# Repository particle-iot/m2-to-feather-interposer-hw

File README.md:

## M.2 to Feather socket Interposer adapter

### Summary:
Many of our customers have scaled on particle using the feather form factor in order to swap out between Cellular and WiFi products. Unfortunately we are seeing challenges with Cat M1 and the modem sizes that we can offer in the feather form factor. The SA team would like to propose an interposer board between a Particle M.2 Som to an interposer board that can be inserted into a feather socket on a customers PCB.

We recognize our customers may not be able to take advantage of the interposer board if their mechanical assembly does not accommodate the addition Z height and Width required by the addition of an interposer board and an M.2 Som

The interposer board will need to replicate some of the features not found on the M.2 Soms

#### Features:
* Nano SIM Tray
* PMIC, Same PMIC on Boron
* 3.3V@1A Buck regulator like Boron
* Top or Side pressed MODE and RESET buttons
* Enable pin support
* MCO/Board outline is slightly larger than a feather board due to SMT header.

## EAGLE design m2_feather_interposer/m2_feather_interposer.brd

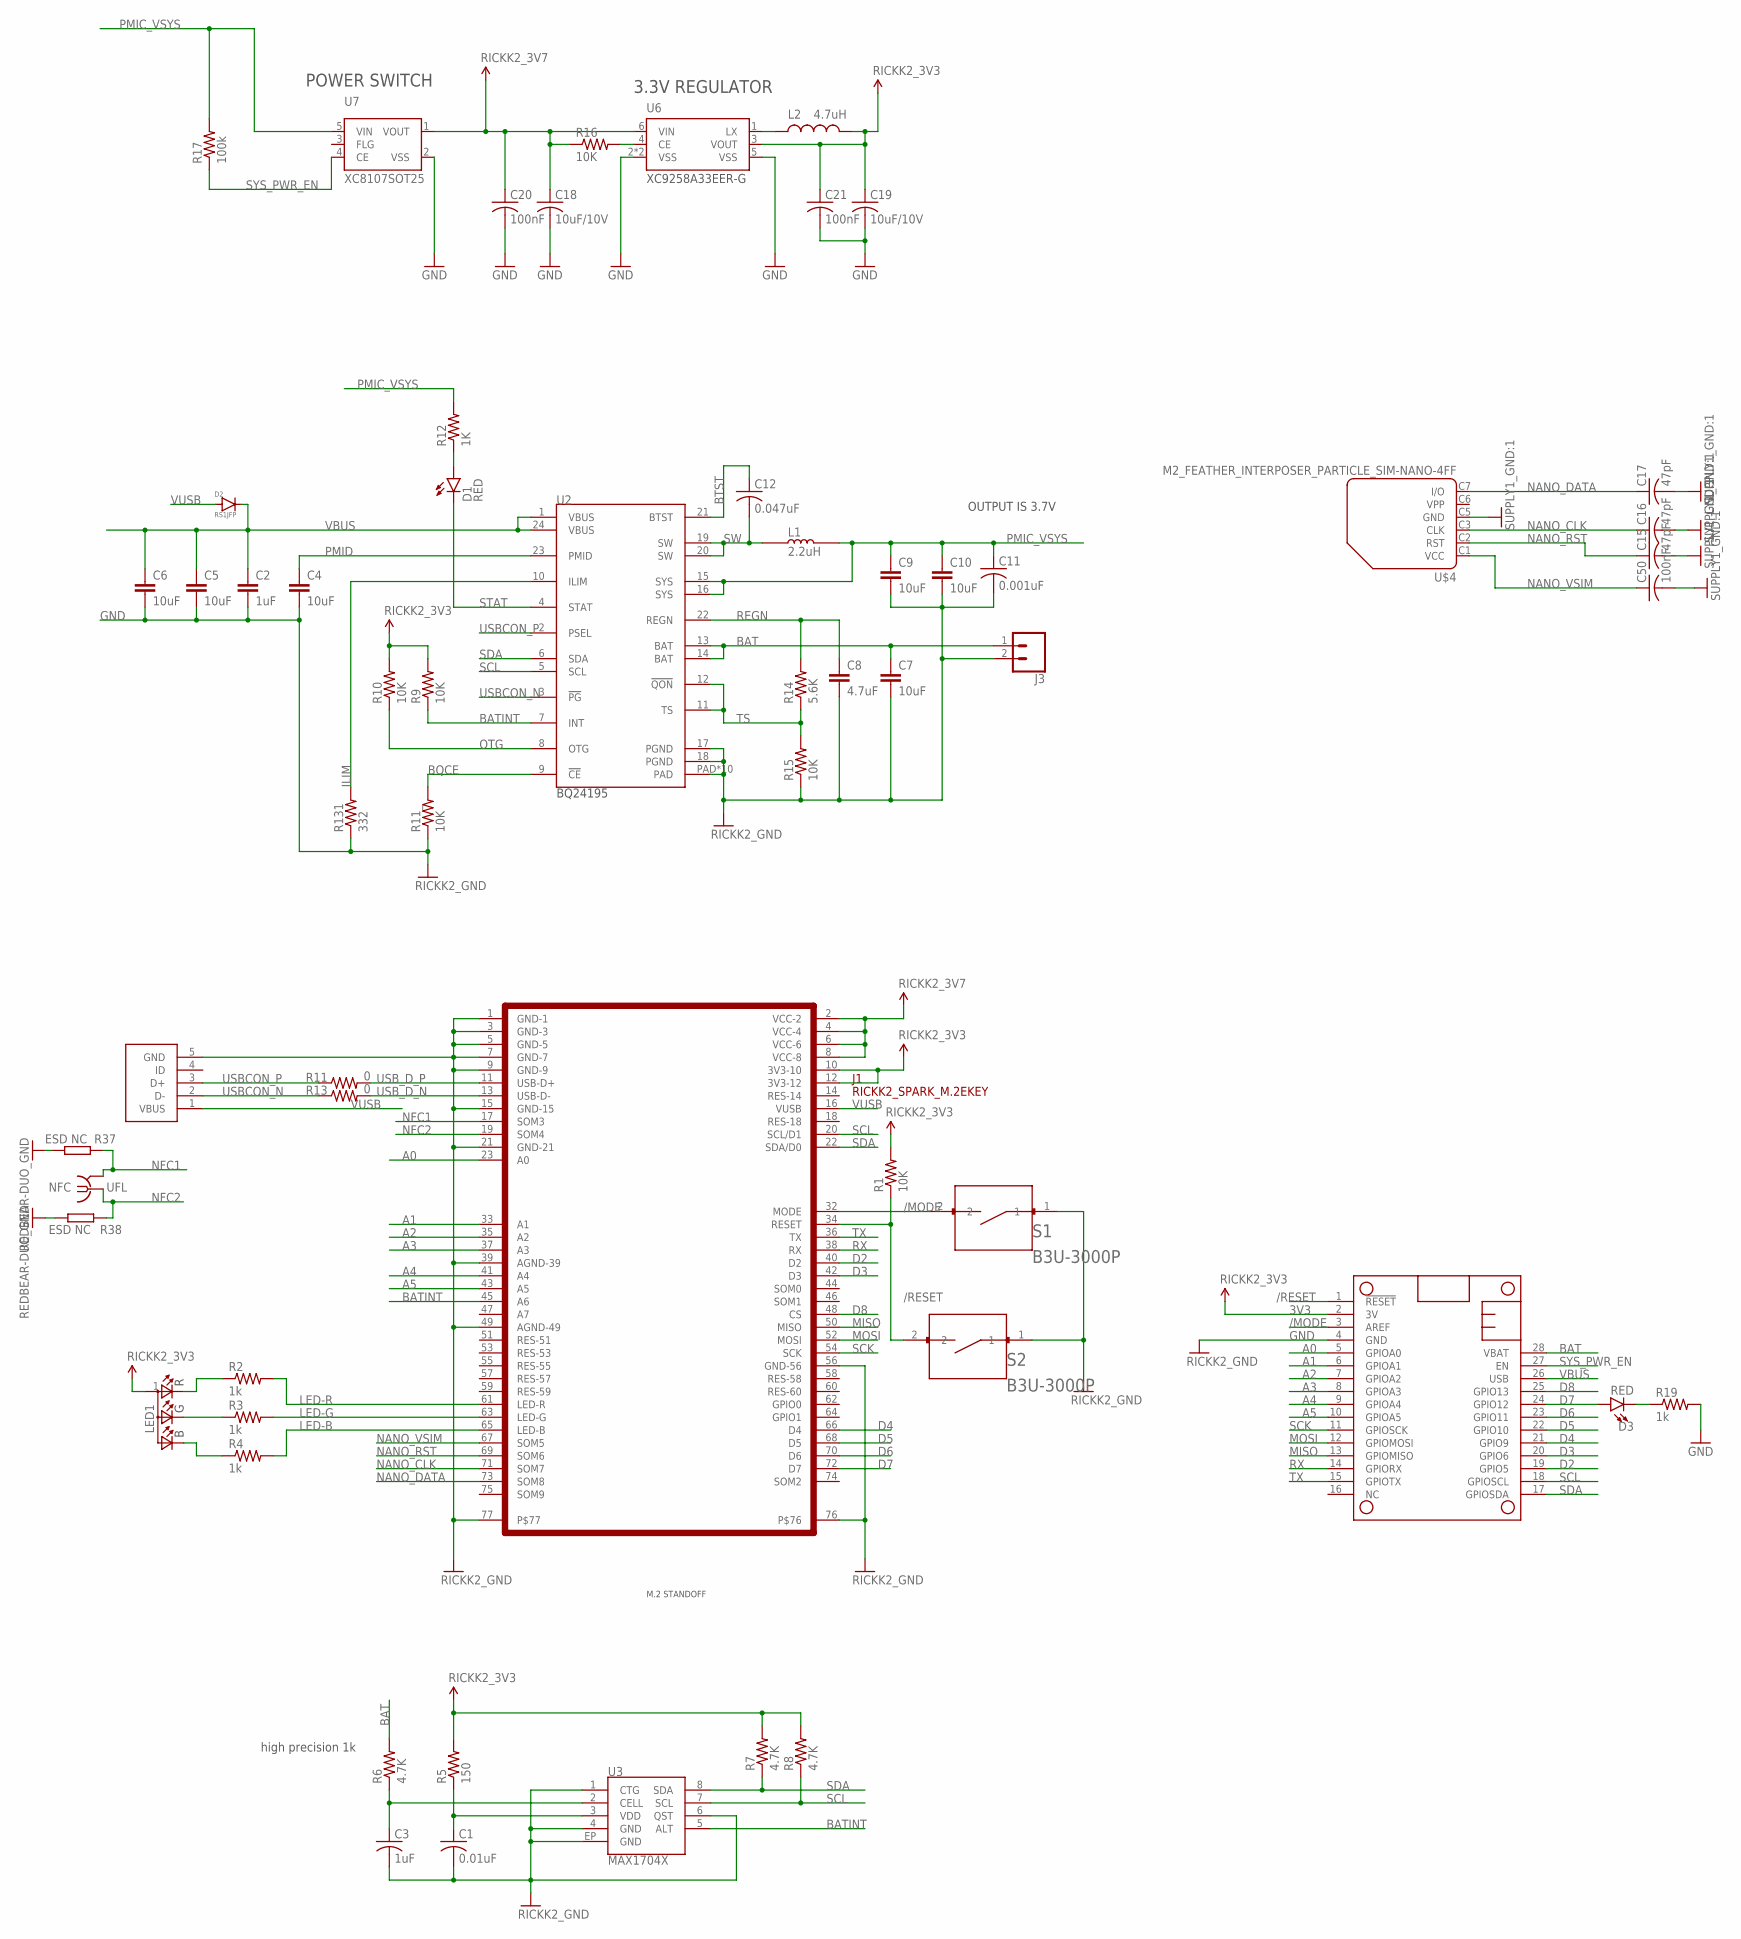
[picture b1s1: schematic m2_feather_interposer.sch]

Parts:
C1: 0.01uF; C0402
C2: 1uF; 0603-CAP
C3: 1uF; C0402
C4, C5, C6, C7, C9, C10: 10uF; RICKK2_0603-CAP
C8: 4.7uF; RICKK2_0603-CAP
C11: 0.001uF; C0402
C12: 0.047uF; C0402
C15, C16, C17: 47pF; PARTICLE_C0201_B
C18, C19: 10uF/10V; C0603K
C20: 100nF; C0603K
C21: 100nF; C0201_B
C50: 100nF; PARTICLE_C0201_B
D1: RED; RICKK2_LED-0603
D2: RS1JFP; RICKK2_SOD-123HE-ON
D3: RED; LED-0603
J1: RICKK2_SPARK_M.2EKEY; RICKK2_SPARK_M.2EKEY-LESS-CREAM
J3: CONN_02; 1X02
L1: 2.2uH; RICKK2_1008-BOURNS
L2: 4.7uH; INDUCTOR-VLS-E
LED1: RICKK2_LED-RGB-CREE-SMD
MS1: MICROBUILDER_FEATHERWINGSMT_BTM_FEATHER; SMT_BTM_FEATHERWING
NFC: UFL; PARTICLE_IPEX-20279-001E
R1, R9, R10, R11_, R15, R16: 10K; R0402
R2, R3, R4, R19: 1k; R0402
R5: 150; R0402
R6, R7, R8: 4.7K; R0402
R11, R13: 0; R0402
R12: 1K; R0402
R14: 5.6K; R0402
R17: 100k; R0402
R37, R38: ESD NC; REDBEAR_R-0402S
R131: 332; R0402
S1, S2: B3U-3000P; SW_B3U-3000P
U2: BQ24195; RICKK2_24VFQN-TI
U3: MAX1704X; TDFN-8
U6: XC9258A33EER-G; USP-6C
U7: XC8107SOT25; SOT25
U$1: RICKK2_M2-STANDOFF
U$3: RICKK2_USB-MICRO-B-SOCKET-AMPHENOL; RICKK2_USB-B-SMT-AMPHENOL
U$4: M2_FEATHER_INTERPOSER_PARTICLE_SIM-NANO-4FF; M2_FEATHER_INTERPOSER_PARTICLE_GCT-SIM8100

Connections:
3V3: C19.1, C21.1, J1.10 (3V3-10), J1.12 (3V3-12), L2.P$2 (2), LED1.1 (A), MS1.2 (3V), R1.2, R5.2, R7.2, R8.2, R9.2, R10.2, U6.3 (VOUT)
3V7: C18.1, C20.1, J1.2 (VCC-2), J1.4 (VCC-4), J1.6 (VCC-6), J1.8 (VCC-8), R16.1, U6.6 (VIN), U7.1 (VOUT)
/MODE: J1.32 (MODE), MS1.3 (AREF), S1.2
/RESET: J1.34 (RESET), MS1.1 (!RESET), R1.1, S2.2
A0: J1.23 (A0), MS1.5 (GPIOA0)
A1: J1.33 (A1), MS1.6 (GPIOA1)
A2: J1.35 (A2), MS1.7 (GPIOA2)
A3: J1.37 (A3), MS1.8 (GPIOA3)
A4: J1.41 (A4), MS1.9 (GPIOA4)
A5: J1.43 (A5), MS1.10 (GPIOA5)
BAT: C7.1, J3.1, MS1.28 (VBAT), R6.2, U2.13 (BAT), U2.14 (BAT)
BATINT: J1.45 (A6), R9.1, U2.7 (INT), U3.5 (ALT)
BQCE: R11_.2, U2.9 (!CE)
BTST: C12.1, U2.21 (BTST)
D2: J1.40 (D2), MS1.19 (GPIO5)
D3: J1.42 (D3), MS1.20 (GPIO6)
D4: J1.66 (D4), MS1.21 (GPIO9)
D5: J1.68 (D5), MS1.22 (GPIO10)
D6: J1.70 (D6), MS1.23 (GPIO11)
D7: D3.A, J1.72 (D7), MS1.24 (GPIO12)
D8: J1.48 (CS), MS1.25 (GPIO13)
GND: C1.2, C2.2, C3.2, C4.2, C5.2, C6.2, C7.2, C8.2, C9.2, C10.2, C11.2, C15.2, C16.2, C17.2, C18.2, C19.2, C20.2, C21.2, C50.2, J1.1 (GND-1), J1.3 (GND-3), J1.5 (GND-5), J1.7 (GND-7), J1.9 (GND-9), J1.15 (GND-15), J1.21 (GND-21), J1.39 (AGND-39), J1.49 (AGND-49), J1.56 (GND-56), J1.76, J1.77, J3.2, MS1.4 (GND), R11_.1, R15.1, R19.2, R37.2, R38.1, R131.1, S1.1, S2.1, U2.17 (PGND), U2.18 (PGND), U2.PAD, U2.PAD@1 (PAD), U2.PAD@2 (PAD), U2.PAD@3 (PAD), U2.PAD@4 (PAD), U2.PAD@5 (PAD), U2.PAD@6 (PAD), U2.PAD@7 (PAD), U2.PAD@8 (PAD), U2.PAD@9 (PAD), U3.1 (CTG), U3.4 (GND), U3.6 (QST), U3.EP (GND), U6.2 (VSS), U6.5 (VSS), U6.P$1 (VSS), U7.2 (VSS), U$3.5 (GND), U$4.C5 (GND)
ILIM: R131.2, U2.10 (ILIM)
LED-B: J1.65 (LED-B), R4.2
LED-G: J1.63 (LED-G), R3.2
LED-R: J1.61 (LED-R), R2.2
MISO: J1.50 (MISO), MS1.13 (GPIOMISO)
MOSI: J1.52 (MOSI), MS1.12 (GPIOMOSI)
unnamed: LED1.3 (G), R3.1
unnamed: C3.1, R6.1, U3.2 (CELL)
unnamed: C1.1, R5.1, U3.3 (VDD)
unnamed: LED1.4 (R), R2.1
unnamed: D1.A, R12.1
unnamed: LED1.2 (B), R4.1
unnamed: R16.2, U6.4 (CE)
unnamed: D3.C, R19.1
unnamed: L2.P$1 (1), U6.1 (LX)
NANO_CLK: C16.1, J1.71 (SOM7), U$4.C3 (CLK)
NANO_DATA: C17.1, J1.73 (SOM8), U$4.C7 (I/O)
NANO_RST: C15.1, J1.69 (SOM6), U$4.C2 (RST)
NANO_VSIM: C50.1, J1.67 (SOM5), U$4.C1 (VCC)
NFC1: J1.17 (SOM3), NFC.2@1 (GND), NFC.2@2 (GND), R37.1
NFC2: J1.19 (SOM4), NFC.1, R38.2
OTG: R10.1, U2.8 (OTG)
PMIC_VSYS: C9.1, C10.1, C11.1, L1.2, R12.2, R17.2, U2.15 (SYS), U2.16 (SYS), U7.5 (VIN)
PMID: C4.1, U2.23 (PMID)
REGN: C8.1, R14.2, U2.22 (REGN)
RX: J1.38 (RX), MS1.14 (GPIORX)
SCK: J1.54 (SCK), MS1.11 (GPIOSCK)
SCL: J1.20 (SCL/D1), MS1.18 (GPIOSCL), R8.1, U2.5 (SCL), U3.7 (SCL)
SDA: J1.22 (SDA/D0), MS1.17 (GPIOSDA), R7.1, U2.6 (SDA), U3.8 (SDA)
STAT: D1.C, U2.4 (STAT)
SW: C12.2, L1.1, U2.19 (SW), U2.20 (SW)
SYS_PWR_EN: MS1.27 (EN), R17.1, U7.4 (CE)
TS: R14.1, R15.2, U2.11 (TS), U2.12 (!QON)
TX: J1.36 (TX), MS1.15 (GPIOTX)
USBCON_N: R13.1, U2.3 (!PG), U$3.2 (D-)
USBCON_P: R11.1, U2.2 (PSEL), U$3.3 (D+)
USB_D_N: J1.13 (USB-D-), R13.2
USB_D_P: J1.11 (USB-D+), R11.2
VBUS: C2.1, C5.1, C6.1, D2.1 (CATHODE), MS1.26 (USB), U2.1 (VBUS), U2.24 (VBUS)
VUSB: D2.2 (ANODE), J1.16 (VUSB), U$3.1 (VBUS)

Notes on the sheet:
3.3V REGULATOR
POWER SWITCH
OUTPUT IS 3.7V
high precision 1k

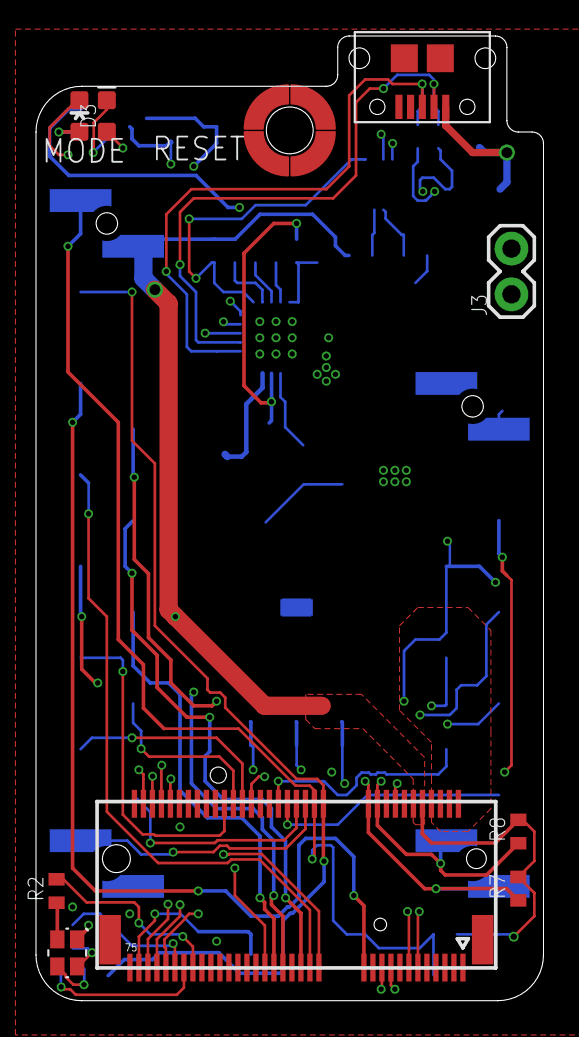
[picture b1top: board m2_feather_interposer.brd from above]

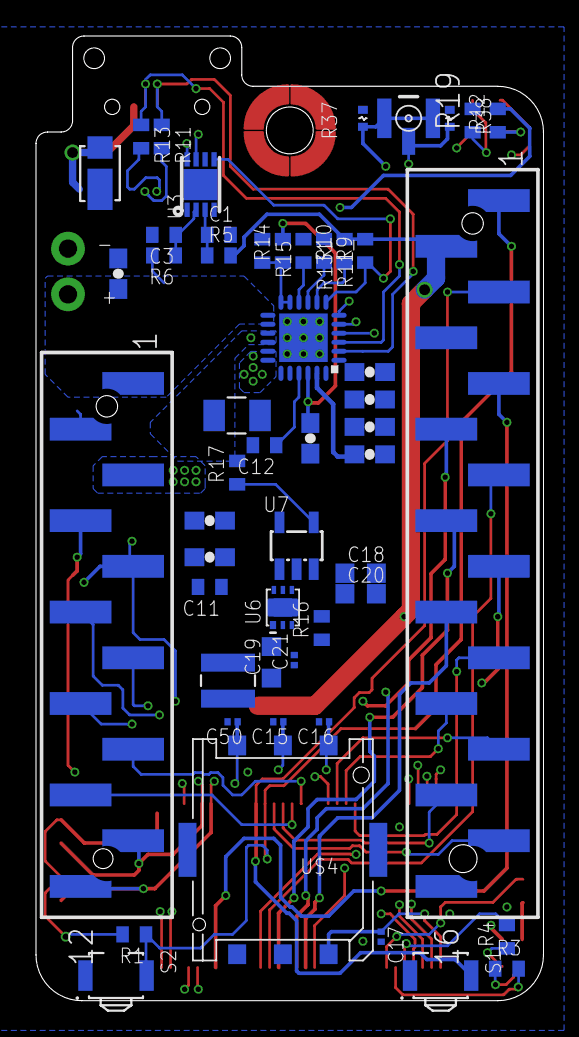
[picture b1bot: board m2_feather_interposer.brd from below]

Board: 4 copper layers, 28.2 x 53.6 mm, 61 parts (50 on the bottom side), 62 nets.

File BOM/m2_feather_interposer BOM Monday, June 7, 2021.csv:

"Qty";"Value";"Device";"Package";"Parts";"Description";"AVAILABILITY";"DESCRIPTION";"MF";"MP";"PACKAGE";"POPULARITY";"PRICE";"PROD-ID";"PROD_ID";"PURCHASE-URL";"SPICEPREFIX";"VALUE";
"1";"";"CONN_02";"1X02";"J3";"Multi connection point. Often used as Generic Header-pin footprint for 0.1 inch spaced/style header connections";"";"";"";"";"";"";"";"";"";"";"";"";
"2";"0";"R-US_R0402";"R0402";"R11, R13";"RESISTOR, American symbol";"";"";"";"";"";"";"";"";"";"";"";"";
"1";"0.001uF";"C-USC0402";"C0402";"C11";"CAPACITOR, American symbol";"";"";"";"";"";"";"";"";"";"";"";"";
"1";"0.01uF";"C-USC0402";"C0402";"C1";"CAPACITOR, American symbol";"";"";"";"";"";"";"";"";"";"";"";"";
"1";"0.047uF";"C-USC0402";"C0402";"C12";"CAPACITOR, American symbol";"";"";"";"";"";"";"";"";"";"";"";"";
"1";"100k";"R-US_R0402";"R0402";"R17";"RESISTOR, American symbol";"";"";"";"";"";"";"";"";"";"";"";"";
"1";"100nF";"C-USC0201_B";"C0201_B";"C21";"Capacitor";"";"";"";"";"";"";"";"";"";"";"";"";
"1";"100nF";"C-USC0603K";"C0603K";"C20";"CAPACITOR, American symbol";"";"";"";"";"";"5";"";"";"";"";"C";"";
"1";"100nF";"PARTICLE_C-USC0201_B";"PARTICLE_C0201_B";"C50";"Capacitor";"";"";"";"";"";"";"";"";"";"";"";"";
"6";"10K";"R-US_R0402";"R0402";"R1, R9, R10, R11_, R15, R16";"RESISTOR, American symbol";"";"";"";"";"";"";"";"";"";"";"";"";
"6";"10uF";"RICKK2_CAP-10UF-0603";"RICKK2_0603-CAP";"C4, C5, C6, C7, C9, C10";"CAP CER 10UF 16V X5R 0805 $ 0.21";"";"";"";"";"";"";"";"";"";"";"";"10uF";
"2";"10uF/10V";"C-USC0603K";"C0603K";"C18, C19";"CAPACITOR, American symbol";"";"";"";"";"";"5";"";"";"";"";"C";"";
"1";"150";"R-US_R0402";"R0402";"R5";"RESISTOR, American symbol";"";"";"";"";"";"";"";"";"";"";"";"";
"1";"1K";"R-US_R0201_B";"C0201_B";"R19";"0402 Resistor";"";"";"";"";"";"";"";"";"";"";"";"";
"1";"1K";"R-US_R0402";"R0402";"R12";"RESISTOR, American symbol";"";"";"";"";"";"";"";"";"";"";"";"";
"3";"1k";"R-US_R0402";"R0402";"R2, R3, R4";"RESISTOR, American symbol";"";"";"";"";"";"";"";"";"";"";"";"";
"1";"1uF";"C-USC0402";"C0402";"C3";"CAPACITOR, American symbol";"";"";"";"";"";"";"";"";"";"";"";"";
"1";"1uF";"CAP-1UF-0603.DEV";"0603-CAP";"C2";"CAP CER 1UF 25V X7R 0603 $ 0.10";"";"";"";"";"";"";"";"";"";"";"";"1uF";
"1";"2.2uH";"RICKK2_INDUCTOR-2.2UH";"RICKK2_1008-BOURNS";"L1";"2.2uH inductor $0.31 **not ordered yet**";"";"";"";"";"";"";"";"";"";"";"";"2.2uH";
"1";"332";"R-US_R0402";"R0402";"R13_";"RESISTOR, American symbol";"";"";"";"";"";"";"";"";"";"";"";"";
"3";"4.7K";"R-US_R0402";"R0402";"R6, R7, R8";"RESISTOR, American symbol";"";"";"";"";"";"";"";"";"";"";"";"";
"1";"4.7uF";"RICKK2_CAP-4.7UF-0603";"RICKK2_0603-CAP";"C8";"Murata X5R series";"";"";"";"";"";"";"";"";"";"";"";"4.7uF";
"1";"4.7uH";"INDUCTOR-SPARKFUNVLS3012ET-4R7M";"INDUCTOR-VLS-E";"L2";"Inductors";"";"";"";"";"";"";"";"";"";"";"";"";
"3";"47pF";"PARTICLE_C-USC0201_B";"PARTICLE_C0201_B";"C15, C16, C17";"Capacitor";"";"";"";"";"";"";"";"";"";"";"";"";
"1";"5.6K";"R-US_R0402";"R0402";"R14";"RESISTOR, American symbol";"";"";"";"";"";"";"";"";"";"";"";"";
"2";"B3U-3000P";"B3U-3000P";"SW_B3U-3000P";"S1, S2";"Ultra-small Surface-mounting Tactile Switches with High Contact Reliability Check prices";"Warning";" Tactile Switch SPST-NO Side Actuated Surface Mount, Right Angle ";"Omron";"B3U-3100P-B";"Custom Package Omron";"";"None";"";"";"https://pricing.snapeda.com/search/part/B3U-3100P-B/?ref=eda";"";"";
"1";"BQ24195";"RICKK2_BQ24195";"RICKK2_24VFQN-TI";"U2";"Texas Instruments BQ24195LRGER $2.93";"";"";"";"";"";"";"";"";"";"";"";"BQ24195";
"2";"ESD NC";"REDBEAR_RES0402S";"REDBEAR_R-0402S";"R37, R38";"RES";"";"";"";"";"";"";"";"";"";"";"";"";
"1";"M2_FEATHER_INTERPOSER_PARTICLE_SIM-NANO-4FF";"M2_FEATHER_INTERPOSER_PARTICLE_SIM-NANO-4FF";"M2_FEATHER_INTERPOSER_PARTICLE_GCT-SIM8100";"U$4";"SIM NANO 4FF";"";"";"";"";"";"";"";"";"";"";"";"";
"1";"MAX1704X";"MAX1704X";"TDFN-8";"U3";"MAX17043/MAX17044: Battery Fuel Guage (43 is 1cell, 44 is 2cell)";"";"";"";"";"";"";"";"IC-10399";"";"";"";"";
"1";"MICROBUILDER_FEATHERWINGSMT_BTM_FEATHER";"MICROBUILDER_FEATHERWINGSMT_BTM_FEATHER";"SMT_BTM_FEATHERWING";"MS1";"";"";"";"";"";"";"";"";"";"";"";"";"";
"1";"RED";"LED-RED0603";"LED-0603";"D3";"Red SMD LED";"";"";"";"";"";"";"";"";"DIO-00819";"";"";"RED";
"1";"RED";"RICKK2_LED-RED";"RICKK2_LED-0603";"D1";"LED RED CLEAR 0603 SMD $0.41";"";"";"";"";"";"";"";"";"";"";"";"RED";
"1";"RICKK2_LED-RGB-CREE-SMD";"RICKK2_LED-RGB-CREE-SMD";"RICKK2_LED-RGB-CREE-SMD";"LED1";"LED RGB DIFFUSED 4SMD $ 0.35";"";"";"";"";"";"";"";"";"";"";"";"";
"1";"RICKK2_M2-STANDOFF";"RICKK2_M2-STANDOFF";"RICKK2_M2-STANDOFF";"U$1";"https://www.digikey.com/product-detail/en/jae-electronics/SM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";"";"";"";"";"";"";"";"";"";"";"";"";
"1";"RICKK2_SPARK_M.2EKEY";"RICKK2_SPARK_M.2EKEY";"RICKK2_SPARK_M.2EKEY-LESS-CREAM";"J1";"$1.42";"";"";"";"";"";"";"";"";"";"";"";"";
"1";"RICKK2_USB-MICRO-B-SOCKET-AMPHENOL";"RICKK2_USB-MICRO-B-SOCKET-AMPHENOL";"RICKK2_USB-B-SMT-AMPHENOL";"U$3";"CONN USB MICRO B RECPT SMT R/A $0.42";"";"";"";"";"";"";"";"";"";"";"";"";
"1";"RS1JFP";"RICKK2_DIODE-RS1JFP";"RICKK2_SOD-123HE-ON";"D2";"Reverse voltage protection diode - not ordered yet!";"";"";"";"";"";"";"";"";"";"";"";"RS1JFP";
"1";"UFL";"PARTICLE_IPEX-20279-001E";"PARTICLE_IPEX-20279-001E";"NFC";"Ultra Miniature Coaxial SMT RF Receptacle";"";"";"";"";"";"";"";"";"";"";"";"";
"1";"XC8107SOT25";"XC8107SOT25";"SOT25";"U7";"";"";"";"";"";"";"";"";"";"";"";"";"";
"1";"XC9258A33EER-G";"XC9258A33EER-G";"USP-6C";"U6";"1.0A Synchronous Step-Down DC/DC Converters";"";"";"";"";"";"";"";"";"";"";"";"";

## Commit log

2020-10-30 added base files for the project
2020-10-30 added ricks basic som design as a base
2021-01-26 added a whole bunch of stuff, board layout, draft key component placements, added connectors, added components from the boron that were missing.
2021-01-26 modified readme contents to reflect actual design
2021-03-31 all components added and key component placement done, driving through layout draft
2021-04-01 GPIO:draft layout done, LED: draft layout done, Buttons:draft layout done, SIM: draft layout done, NFC: draft layout done. Open items: fuel gauge, pmic, 3.3V reg
2021-04-01 working through pmic, 3.3V and pwr switch layout:
2021-06-10 added draft bom
2025-08-20 Add CC-BY-SA license

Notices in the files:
parts and their libraries:
SparkFun-Connectors: Licensing: Creative Commons ShareAlike 4.0 International - https://creativecommons.org/licenses/by-sa/4.0
